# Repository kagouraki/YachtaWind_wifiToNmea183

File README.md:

# YachtaWind_wifiToNmea183
esp8266 Wifi to Nmea183 converter

This board and firmware is just a nmea183 repeater. It sends all nmea it recieves from a wifi tcp server to the wired Nmea183 devices. It has two wired nmea183 outputs. 
At some point i will write a guide how to use it and understand the leds.  Until then if you have questions open a discussion. 
It is build to recieve the nmea stream from original Norbert Walter's yachta wind sensor project. 
I made some minor modifications to the pcb, 3dprinted parts and software. You can find everything in my gitlab repos.

Thank you

G.

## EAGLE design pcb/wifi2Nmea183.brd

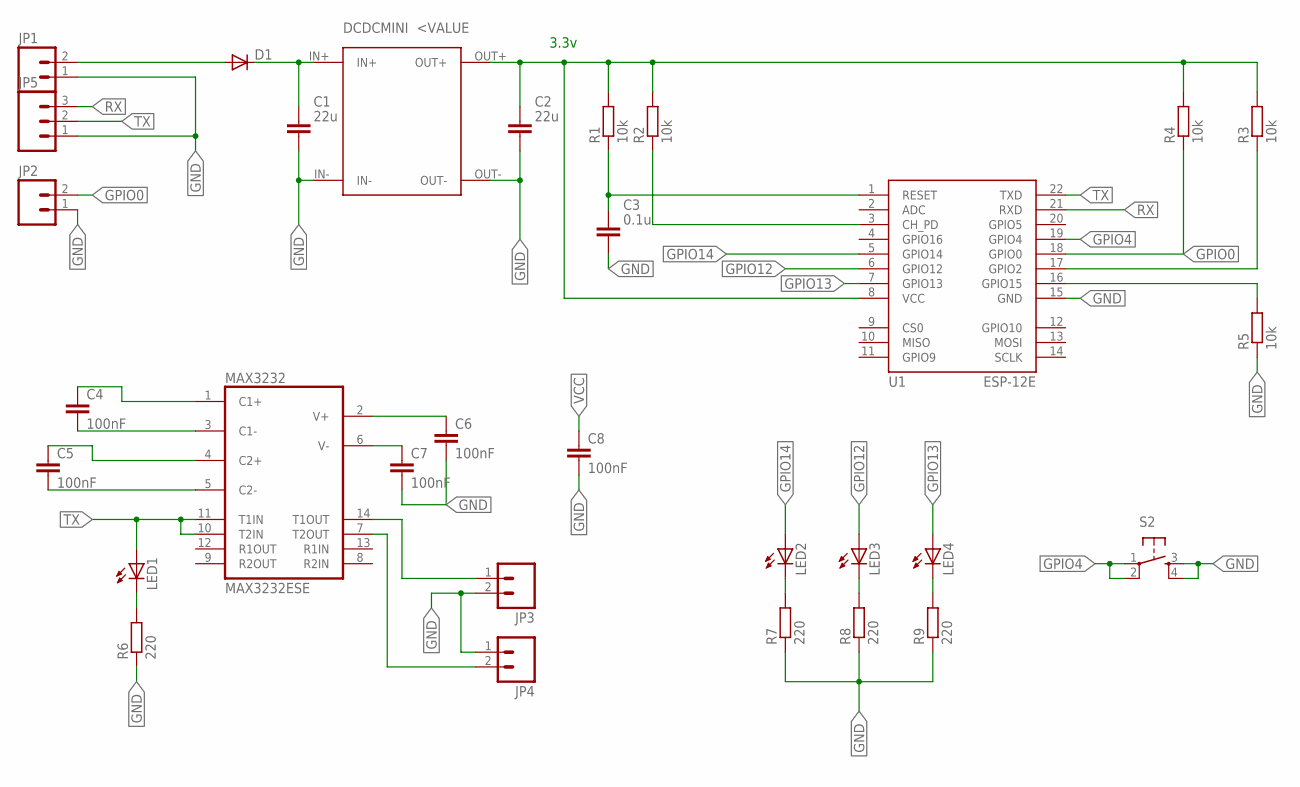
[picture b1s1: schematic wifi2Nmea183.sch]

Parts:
C1, C2: 22u; C1206
C3: 0.1u; C805
C4, C5, C6, C7, C8: 100nF; 0805
D1: DIODE-DO214AC; DO214AC
DCDCMINI: DCDCMINI
JP1, JP2, JP3, JP4: M02LOCK; 1X02_LOCK
JP5: M03LOCK; 1X03_LOCK
LED1, LED2, LED3, LED4: LED3MM
MAX3232: MAX3232ESE; SO16
R1, R2, R3, R4, R5: 10k; R0805
R6, R7, R8, R9: 220; R0805
S2: TAC_SWITCHPTH; TACTILE-PTH
U1: ESP-12E

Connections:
GND: C1.2, C2.2, C3.2, C6.2, C7.2, C8.2, DCDCMINI.IN-, DCDCMINI.OUT-, JP1.1, JP2.1, JP3.2, JP4.1, JP5.1, MAX3232.15 (GND), R5.1, R6.1, R7.1, R8.1, R9.1, S2.3, S2.4, U1.15 (GND)
GPIO0: JP2.2, R4.1, U1.18 (GPIO0)
GPIO4: S2.1, S2.2, U1.19 (GPIO4)
GPIO12: LED3.A, U1.6 (GPIO12)
GPIO13: LED4.A, U1.7 (GPIO13)
GPIO14: LED2.A, U1.5 (GPIO14)
unnamed: D1.A, JP1.2
unnamed: C1.1, D1.C, DCDCMINI.IN+
unnamed: C3.1, R1.1, U1.1 (RESET)
unnamed: R2.1, U1.3 (CH_PD)
unnamed: R3.1, U1.17 (GPIO2)
unnamed: R5.2, U1.16 (GPIO15)
unnamed: C6.1, MAX3232.2 (V+)
unnamed: C7.1, MAX3232.6 (V-)
unnamed: C5.2, MAX3232.5 (C2-)
unnamed: C5.1, MAX3232.4 (C2+)
unnamed: C4.2, MAX3232.3 (C1-)
unnamed: C4.1, MAX3232.1 (C1+)
unnamed: JP3.1, MAX3232.14 (T1OUT)
unnamed: JP4.2, MAX3232.7 (T2OUT)
unnamed: LED1.K (C), R6.2
unnamed: LED2.K (C), R7.2
unnamed: LED3.K (C), R8.2
unnamed: LED4.K (C), R9.2
RX: JP5.3, U1.21 (RXD)
TX: JP5.2, LED1.A, MAX3232.10 (T2IN), MAX3232.11 (T1IN), U1.22 (TXD)
VCC: C2.1, C8.1, DCDCMINI.OUT+, MAX3232.16 (VCC), R1.2, R2.2, R3.2, R4.2, U1.8 (VCC)

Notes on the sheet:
3.3v

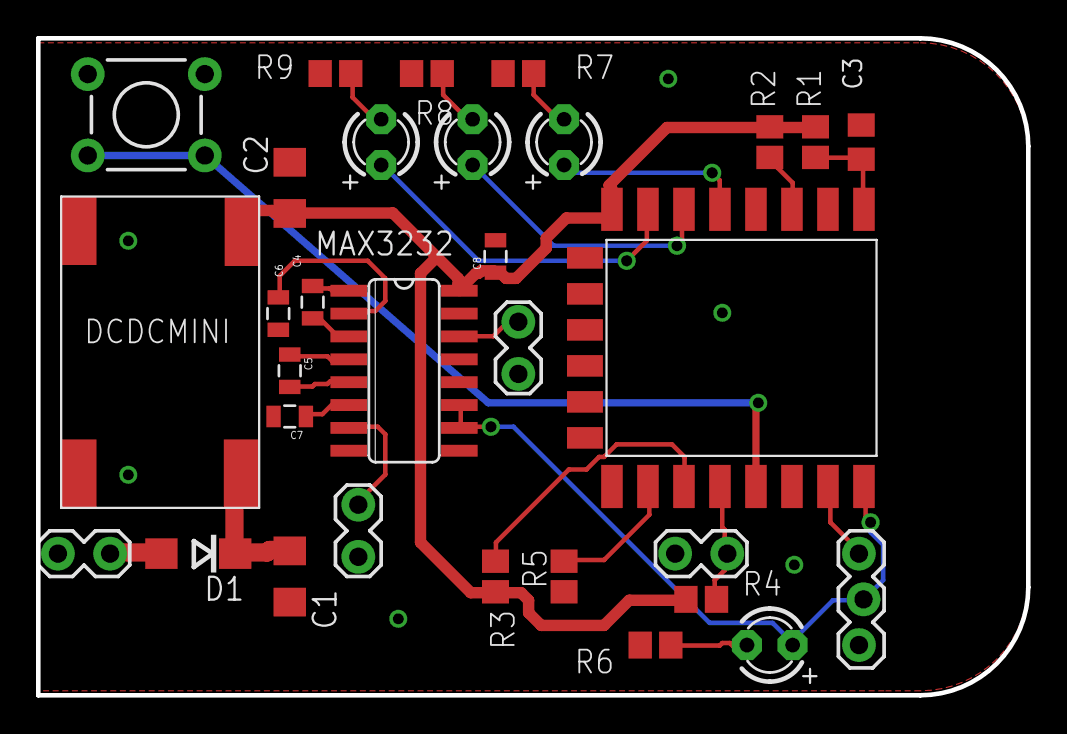
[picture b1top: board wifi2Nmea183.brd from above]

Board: 2 copper layers, 55.0 x 36.5 mm, 31 parts (0 on the bottom side), 27 nets.

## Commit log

2022-06-05 Upload Files
2022-06-05 Forgot something
2022-06-07 Upload of pcb files
2022-06-14 added client.stop when entering config portal
2022-11-26 Added led blink sequence for wrong Ip and port input

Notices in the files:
parts and their libraries:
esp8266: Creative Commons Attribution-ShareAlike 4.0 International
